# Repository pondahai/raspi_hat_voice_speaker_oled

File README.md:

# raspi_hat_voice_speaker_oled

## 簡介
這個Raspberry Pi HAT 整合了麥克風、音訊放大器和OLED螢幕，讓你輕鬆打造語音互動或多媒體應用！

## 設定驅動
在  
`/boot/firmware/config.txt`  
加入  
`dtoverlay=googlevoicehat-soundcard`  
重開機後就成為預設音訊輸入出裝置

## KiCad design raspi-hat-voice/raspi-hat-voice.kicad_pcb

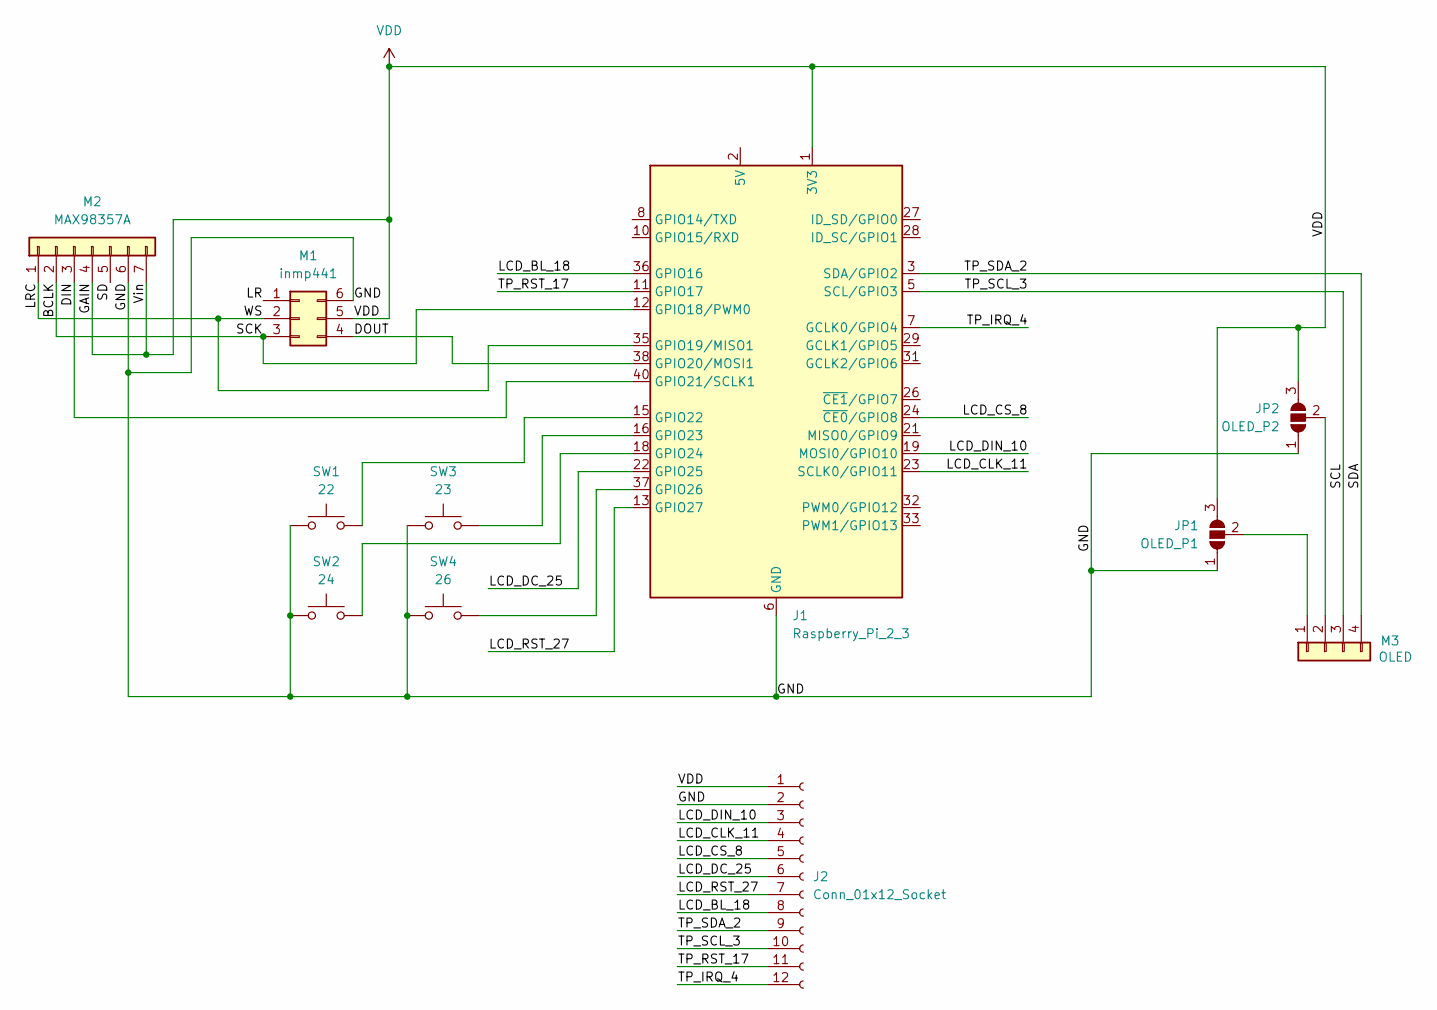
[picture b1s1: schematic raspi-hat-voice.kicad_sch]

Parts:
J1: Raspberry_Pi_2_3; PinSocket_2x20_P2.54mm_Vertical
J2: Conn_01x12_Socket; PinHeader_1x12_P2.54mm_Horizontal
JP1: OLED_P1; SolderJumper-3_P1.3mm_Open_RoundedPad1.0x1.5mm
JP2: OLED_P2; SolderJumper-3_P1.3mm_Open_RoundedPad1.0x1.5mm
M1: inmp441; DIP-6_W7.62mm_LongPads
M2: MAX98357A; PinHeader_1x07_P2.54mm_Vertical
M3: OLED; PinHeader_1x04_P2.54mm_Vertical
SW1: 22; SW_SPST_B3U-3000P-B
SW2: 24; SW_SPST_B3U-3000P-B
SW3: 23; SW_SPST_B3U-3000P-B
SW4: 26; SW_SPST_B3U-3000P-B

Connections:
/BCLK: J1.12 (GPIO18/PWM0), M1.3, M2.2
/DIN: J1.40 (GPIO21/SCLK1), M2.3
/DOUT: J1.38 (GPIO20/MOSI1), M1.4
/GND: J1.6 (GND), J1.9 (GND), J1.14 (GND), J1.20 (GND), J1.25 (GND), J1.30 (GND), J1.34 (GND), J1.39 (GND), J2.2, JP1.1 (A), JP2.1 (A), M1.6, M2.6, SW1.1, SW2.1, SW3.1, SW4.1
/LCD_BL_18: J1.36 (GPIO16), J2.8
/LCD_CLK_11: J1.23 (SCLK0/GPIO11), J2.4
/LCD_CS_8: J1.24 (~CE0/GPIO8), J2.5
/LCD_DC_25: J1.22 (GPIO25), J2.6
/LCD_DIN_10: J1.19 (MOSI0/GPIO10), J2.3
/LCD_RST_27: J1.13 (GPIO27), J2.7
/LR: M1.1
/LRC: J1.35 (GPIO19/MISO1), M1.2, M2.1
/SCL: J1.5 (SCL/GPIO3), J2.10, M3.3
/SD: M2.5
/SDA: J1.3 (SDA/GPIO2), J2.9, M3.4
/TP_IRQ_4: J1.7 (GCLK0/GPIO4), J2.12
/TP_RST_17: J1.11 (GPIO17), J2.11
unnamed: J1.2 (5V), J1.4 (5V)
unnamed: J1.15 (GPIO22), SW1.2
unnamed: J1.16 (GPIO23), SW3.2
unnamed: J1.18 (GPIO24), SW2.2
unnamed: J1.37 (GPIO26), SW4.2
unnamed: JP1.2 (C), M3.1
unnamed: JP2.2 (C), M3.2
VDD: J1.1 (3V3), J1.17 (3V3), J2.1, JP1.3 (B), JP2.3 (B), M1.5, M2.4, M2.7

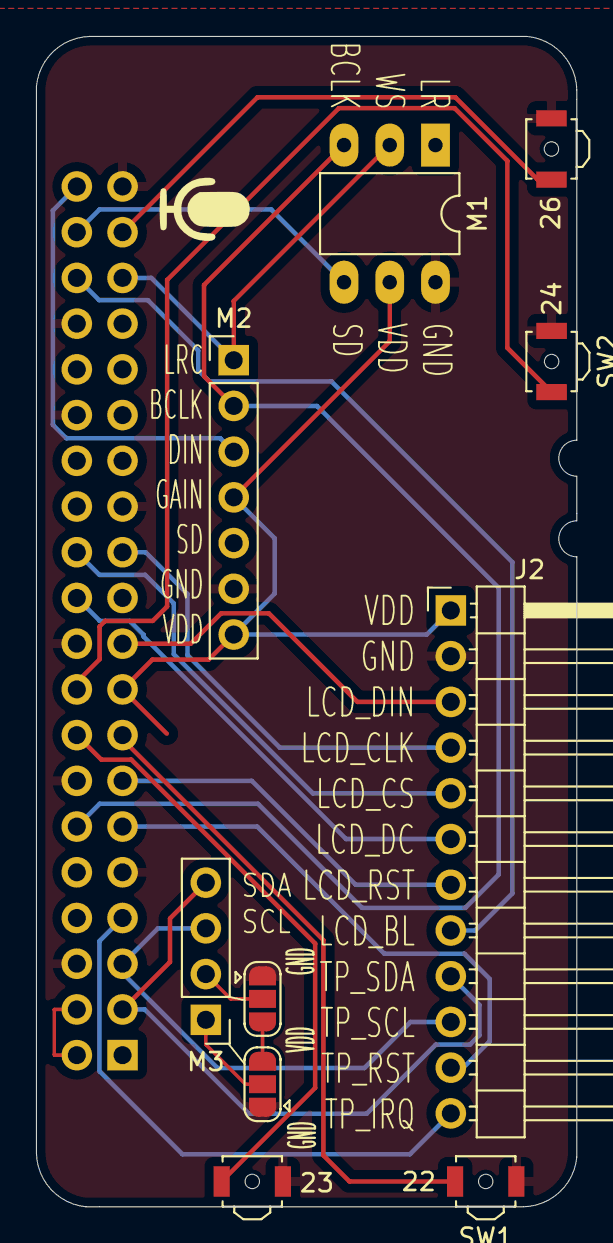
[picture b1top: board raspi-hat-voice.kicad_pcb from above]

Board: 2 copper layers, 30.0 x 65.0 mm, 11 parts (1 on the bottom side), 23 nets.

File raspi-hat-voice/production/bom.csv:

Designator,Footprint,Quantity,Value,LCSC Part #
J1,PinSocket_2x20_P2.54mm_Vertical,1,Raspberry_Pi_2_3,
J2,PinHeader_1x12_P2.54mm_Horizontal,1,Conn_01x12_Socket,
M1,DIP-6_W7.62mm_LongPads,1,inmp441,
M2,PinHeader_1x07_P2.54mm_Vertical,1,MAX98357A,
M3,PinHeader_1x04_P2.54mm_Vertical,1,OLED,
SW1,SW_SPST_B3U-3000P-B,1,22,
SW2,SW_SPST_B3U-3000P-B,1,24,
SW3,SW_SPST_B3U-3000P-B,1,23,
SW4,SW_SPST_B3U-3000P-B,1,26,
